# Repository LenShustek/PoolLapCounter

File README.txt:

pool lap counter

   This is a battery-powered poolside device for counting swim laps. It is a self-contained
   waterproof (well, water-resistant) box with a big button that the swimmer hits, and a
   2-digit display that shows the lap count. The box has suction cups on the bottom, and
   you would typically set it on the edge of the pool deck.

   When you hit the button, the display shows the new lap count for 3 seconds, then goes dark.
   To reset the count to zero, press the button while the count is displayed.
   To show the battery charge percent, press and hold the button.
   
   The circuit is designed to maximize the time between battery charging.  One charge of
   the 0.8 Ah lead-acid battery should last for a year of casual use.

   Major components:
 - a waterproof 4.7" x 4.7" x 3.2" project box with a clear lid
       https://www.mouser.com/ProductDetail/546-1554P2GYCL
   - a big (2") diameter pushbutton with light
       https://smile.amazon.com/gp/product/B01M7PNCO9
   - two 1" super bright red 7-segment LCD digit displays (Kingbright SA10-21SRWA)
   - a constant-current LED driver (STMicroelectronics STP16CPC05)
   - a Teensy LC processor board
   - a 0.8 Ah rechargeable lead-acid battery
   - a 7805 5V regulator
   - miscellaneous transistors, capacitors, resistors, and connectors

L. Shustek, February 2019
Updated April 21, 2019 for printed circuit board version
Updated September 31, 2020 to include battery charge display and circuit tweaks

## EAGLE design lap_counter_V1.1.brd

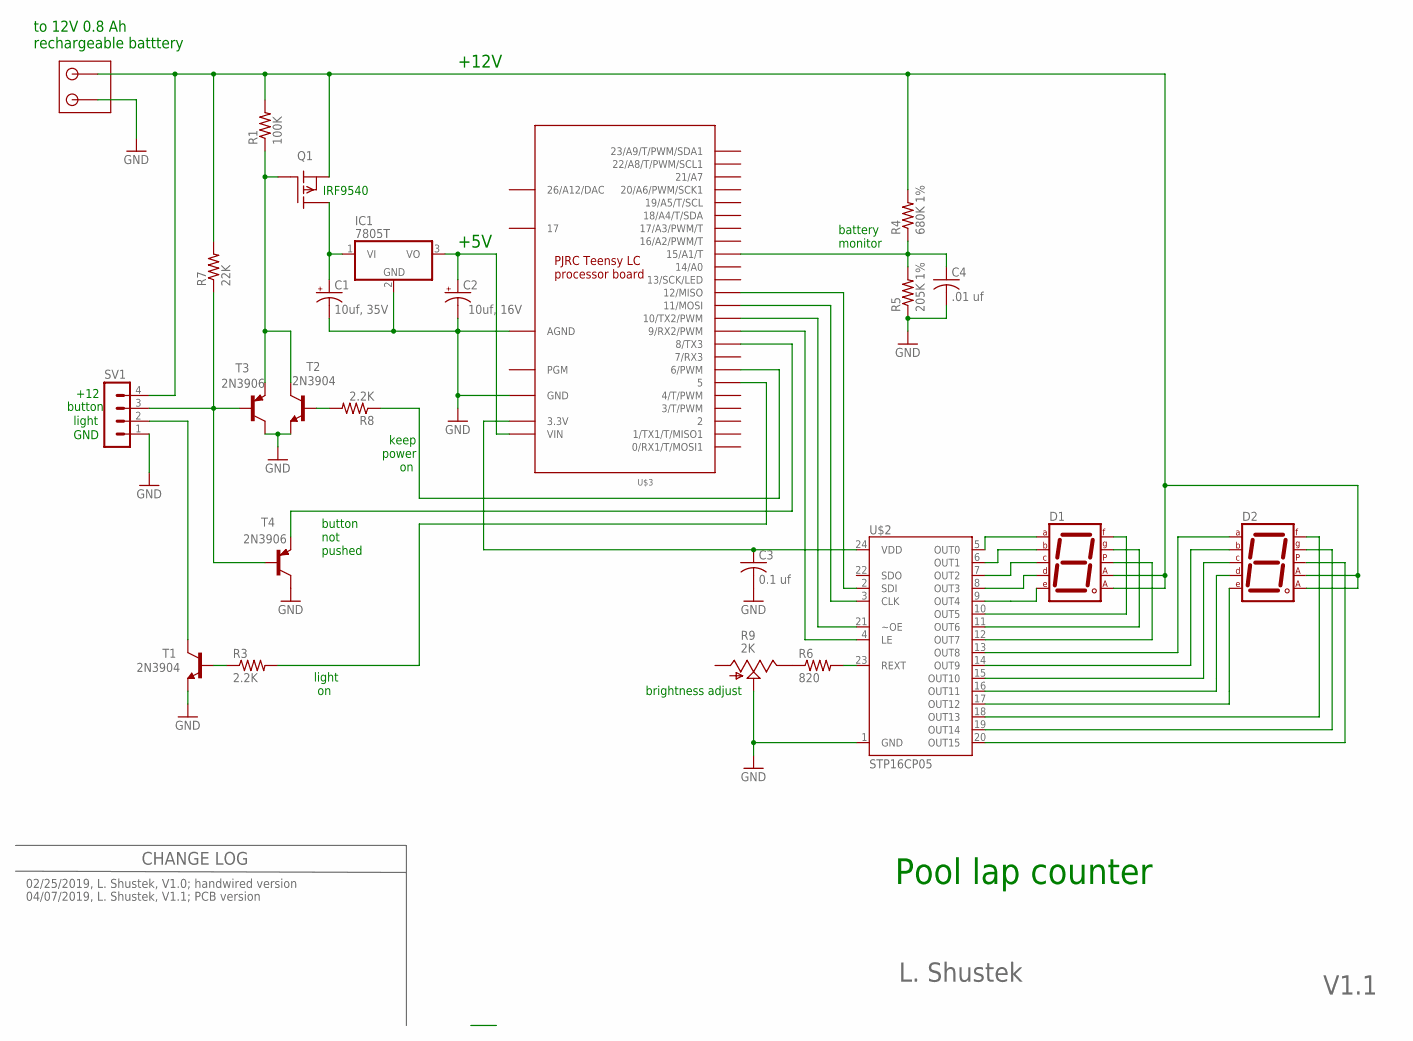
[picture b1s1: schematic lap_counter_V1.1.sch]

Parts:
C1: 10uf, 35V; E2,5-6
C2: 10uf, 16V; E2,5-6
C3: 0.1 uf; C025-030X050
C4: .01 uf; C025-030X050
D1, D2: 7SEG-CA; 7SEG-13
IC1: 7805T; TO220H
Q1: IRF9530; TO220
R1: 100K; 0207/10
R3, R8: 2.2K; 0207/10
R4: 680K 1%; 0207/10
R5: 205K 1%; 0207/10
R6: 820; 0207/10
R7: 22K; 0207/10
R9: 2K; B25P
SV1: MA04-1
T1, T2: 2N3904; TO92-EBC-OVAL
T3, T4: 2N3906; TO92-EBC-OVAL
U$1: CONNECTOR-2PIN; CONNECTOR-2PIN-5MM
U$2: STP16CP05; SO-24DW
U$3: TEENSY_LC_OUTER_ROW; TEENSY3-OUTER_ROW

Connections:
26/A12/DAC: U$3.RESET/DAC (26/A12/DAC)
GND: C1.-, C2.-, C3.2, C4.2, IC1.2 (GND), R5.1, R9.S, SV1.1, T1.E, T2.E, T3.C, T4.C, U$1.P$1, U$2.1 (GND), U$3.AGND, U$3.GND, U$3.GND1 (GND)
unnamed: D1.3 (CA1), D1.8 (CA2), D2.3 (CA1), D2.8 (CA2), Q1.3 (S), R1.2, R4.2, R7.2, SV1.4, U$1.P$2
unnamed: C4.1, R4.1, R5.2, U$3.15/A1 (15/A1/T)
unnamed: Q1.1 (G), R1.1, T2.C, T3.E
unnamed: C1.+, IC1.1 (VI), Q1.2 (D)
unnamed: C2.+, IC1.3 (VO), U$3.VIN
unnamed: R3.1, T1.B
unnamed: R6.1, R9.E
unnamed: R6.2, U$2.23 (REXT)
unnamed: U$2.2 (SDI), U$3.12 (12/MISO)
unnamed: U$2.3 (CLK), U$3.11 (11/MOSI)
unnamed: U$2.21 (~OE), U$3.10 (10/TX2/PWM)
unnamed: U$2.4 (LE), U$3.9 (9/RX2/PWM)
unnamed: D1.7 (A), U$2.5 (OUT0)
unnamed: D1.6 (B), U$2.6 (OUT1)
unnamed: D1.4 (C), U$2.7 (OUT2)
unnamed: D1.2 (D), U$2.8 (OUT3)
unnamed: D1.1 (E), U$2.9 (OUT4)
unnamed: D1.9 (F), U$2.10 (OUT5)
unnamed: D1.10 (G), U$2.11 (OUT6)
unnamed: D2.7 (A), U$2.13 (OUT8)
unnamed: D2.6 (B), U$2.14 (OUT9)
unnamed: D2.4 (C), U$2.15 (OUT10)
unnamed: D2.2 (D), U$2.16 (OUT11)
unnamed: D2.1 (E), U$2.17 (OUT12)
unnamed: D2.9 (F), U$2.18 (OUT13)
unnamed: D2.10 (G), U$2.19 (OUT14)
unnamed: SV1.2, T1.C
unnamed: R8.2, T2.B
unnamed: R8.1, U$3.6 (6/PWM)
unnamed: R7.1, SV1.3, T3.B, T4.B
unnamed: D1.5 (DP), U$2.12 (OUT7)
unnamed: R3.2, U$3.5
unnamed: T4.E, U$3.8 (8/TX3)
unnamed: C3.1, U$2.24 (VDD), U$3.3.3V, U$3.3.3V1 (3.3V)
unnamed: D2.5 (DP), U$2.20 (OUT15)

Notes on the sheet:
Pool lap counter
IRF9540
to 12V 0.8 Ah rechargeable batttery
L. Shustek
+5V
brightness adjust
button not pushed
keep power on
battery monitor
PJRC Teensy LC processor board
light on
+12V
button
light
CHANGE LOG
02/25/2019, L. Shustek, V1.0; handwired version
04/07/2019, L. Shustek, V1.1; PCB version
V1.1
GND
+12

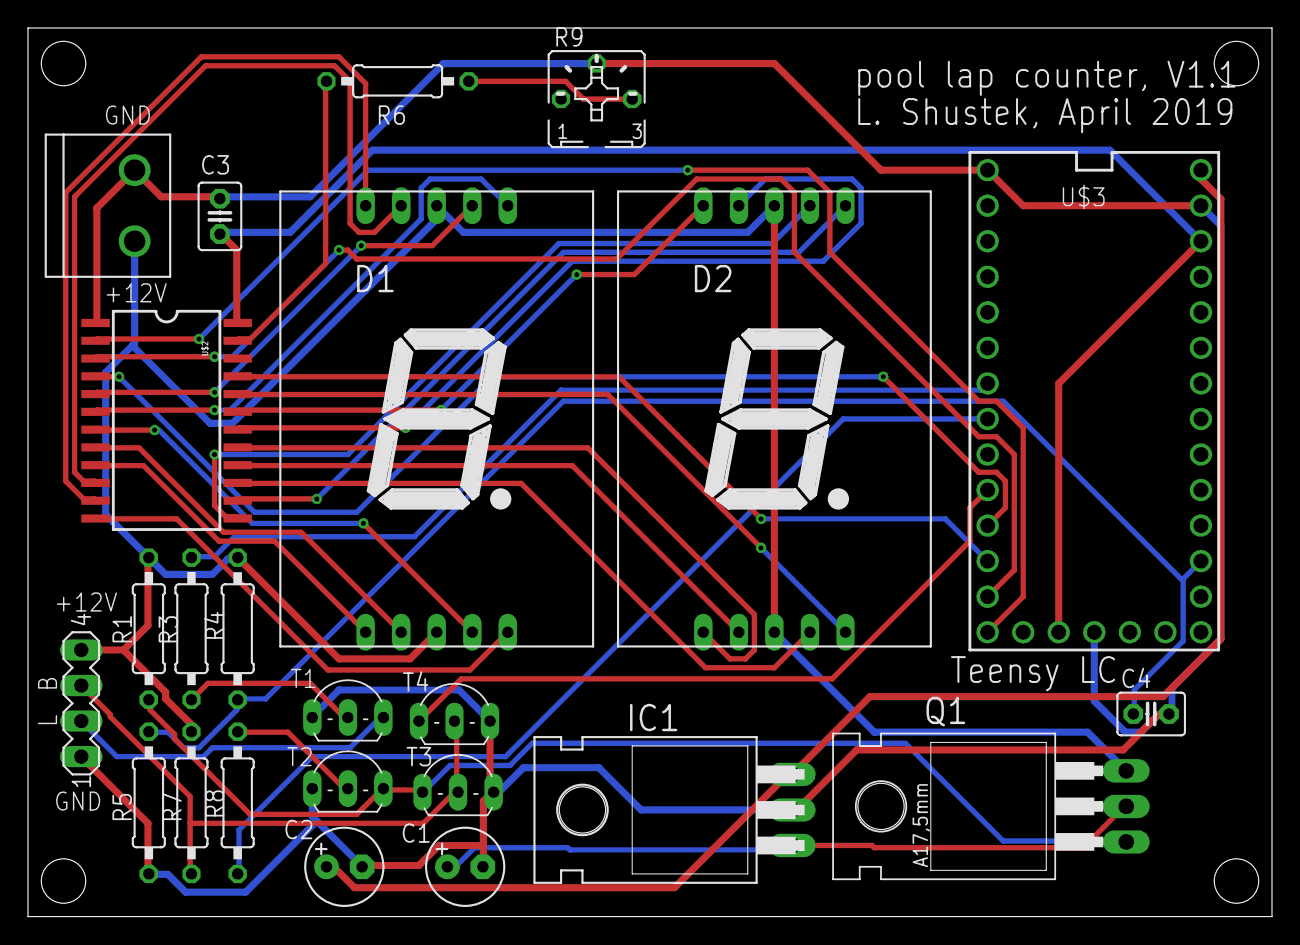
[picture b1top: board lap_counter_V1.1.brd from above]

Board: 2 copper layers, 88.9 x 63.5 mm, 24 parts (0 on the bottom side), 36 nets.

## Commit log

2019-02-26 Initial release
2019-04-22 Updated for printed circuit board version
2022-01-21 minor tweaks for version 1.2; alternate button mechanical design

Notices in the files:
parts and their libraries:
SparkFun-Retired: Licensing: Creative Commons ShareAlike 4.0 International - https://creativecommons.org/licenses/by-sa/4.0
